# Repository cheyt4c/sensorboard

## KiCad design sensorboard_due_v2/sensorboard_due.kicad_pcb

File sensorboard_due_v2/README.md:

# Sensorboard PCB v2

## Changes from v1

 * Schematic will reflect intended PCB design, not current breadboard setup
 * More connectors need to be added on for expansion. I2C address conflict issue (for at least additional IMUs) will need to be addressed.
 * Sensor board will be generic enough to be reused multiple times if needed
 * LED panel connector fix? (missing GND wire)

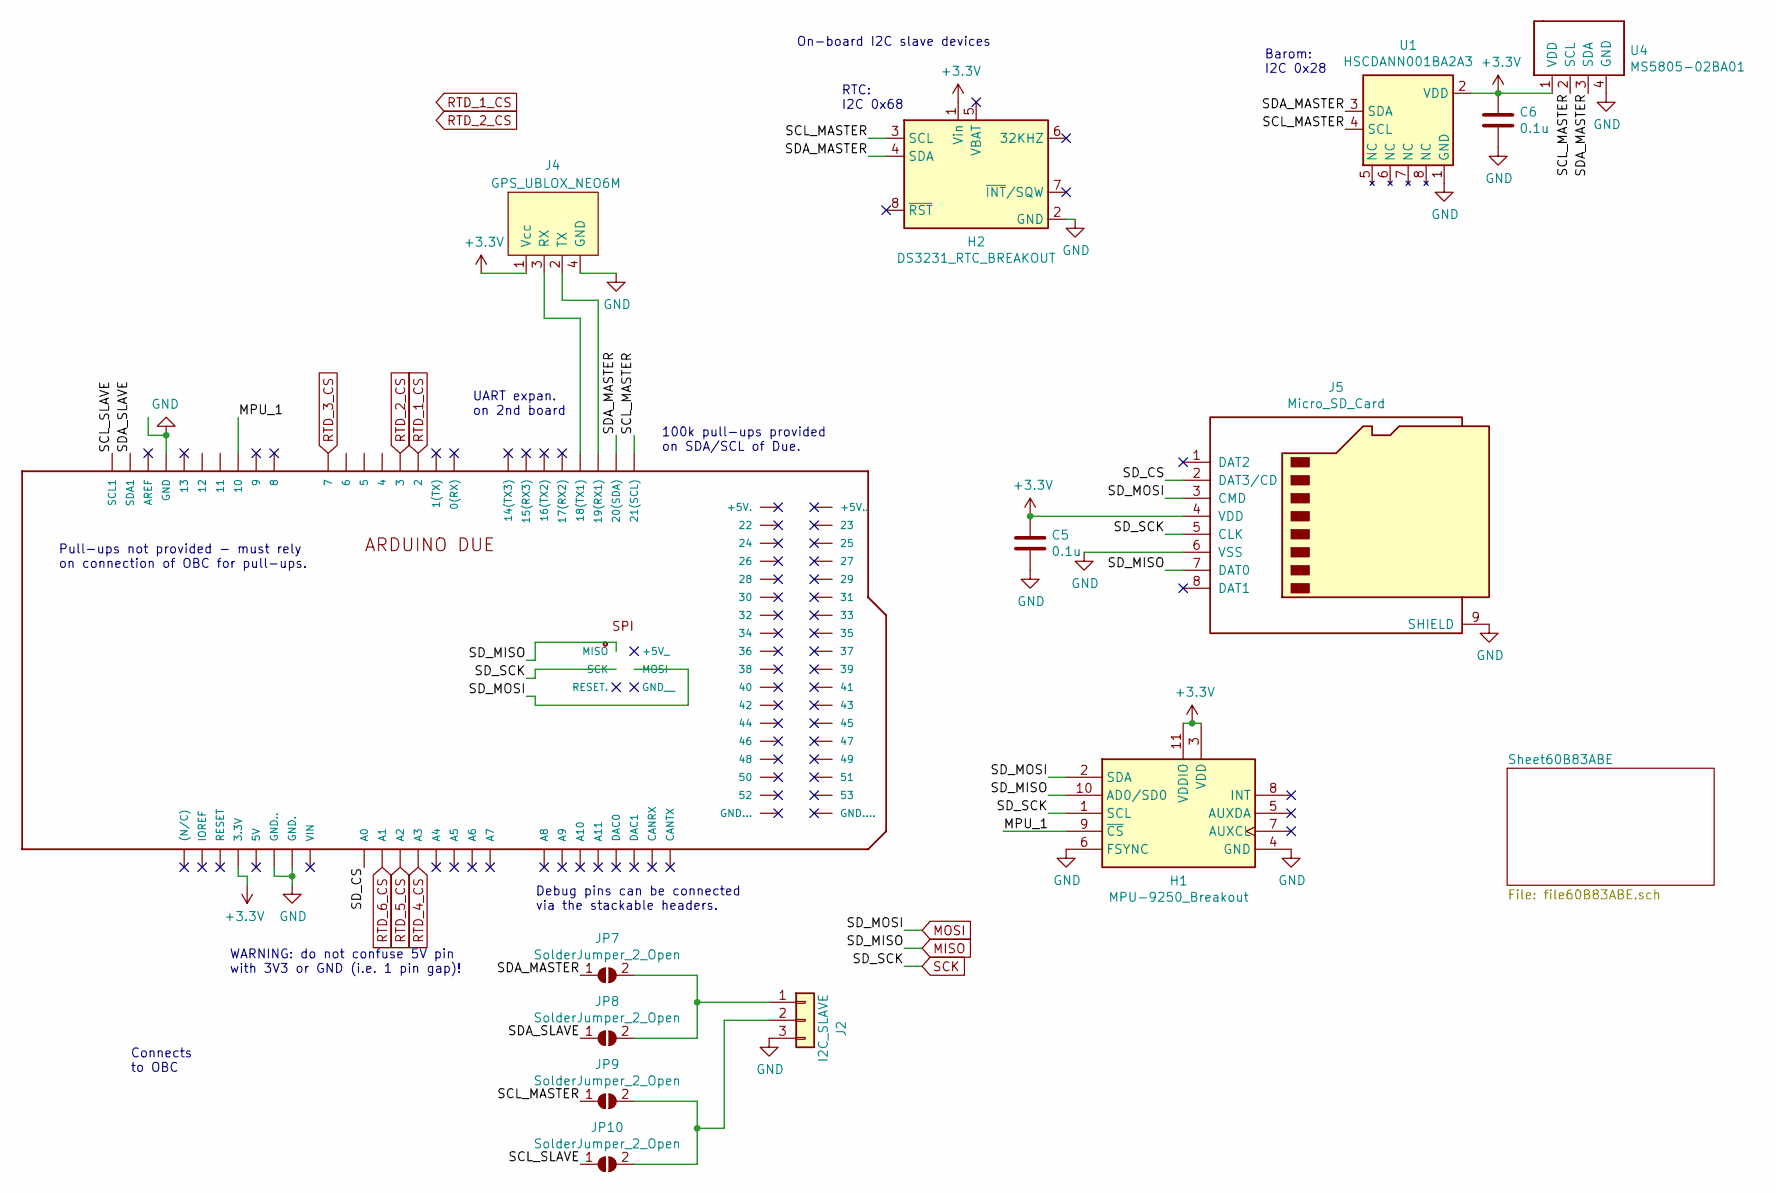
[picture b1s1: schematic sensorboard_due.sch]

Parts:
C5, C6: 0.1u; C_0805_2012Metric_Pad1.15x1.40mm_HandSolder
H1: MPU-9250_Breakout
H2: DS3231_RTC_BREAKOUT; DS3231_RTC_Breakout
J2: I2C_SLAVE; 70553-0002_3P
J4: GPS_UBLOX_NEO6M; 70553-0038_4P
J5: Micro_SD_Card; microSD_HC_Hirose_DM3BT-DSF-PEJS
JP7, JP8, JP9, JP10: SolderJumper_2_Open; SolderJumper-2_P1.3mm_Open_TrianglePad1.0x1.5mm
PCB1: ARDUINO_DUE; ARDUINO_DUE_Shield_wSPI
U1: HSCDANN001BA2A3; HSCDANN001BA2A3_DIP8
U4: MS5805-02BA01

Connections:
+3V3: C5.1, C6.1, H1.3 (VDD), H1.11 (VDDIO), H2.1 (Vin), J4.1 (Vcc), J5.4 (VDD), PCB1.3.3V, U1.2 (VDD), U4.1 (VDD); also elsewhere on the board
/MPU_1: H1.9 (~CS), PCB1.10
/SCL_MASTER: H2.3 (SCL), JP9.1 (A), PCB1.21 (21(SCL)), U1.4 (SCL), U4.2 (SCL)
/SCL_SLAVE: JP10.1 (A), PCB1.SCL1
/SDA_MASTER: H2.4 (SDA), JP7.1 (A), PCB1.20 (20(SDA)), U1.3 (SDA), U4.3 (SDA)
/SDA_SLAVE: JP8.1 (A), PCB1.SDA1
/SD_CS: J5.2 (DAT3/CD), PCB1.A0
GND: C5.2, C6.2, H1.4 (GND), H1.6 (FSYNC), H2.2 (GND), J2.3, J4.4 (GND), J5.6 (VSS), J5.9 (SHIELD), PCB1.GND, PCB1.GND., PCB1.GND.., U1.1 (GND), U4.4 (GND); also elsewhere on the board
MISO: H1.10 (AD0/SD0), J5.7 (DAT0), PCB1.MISO; also elsewhere on the board
MOSI: H1.2 (SDA), J5.3 (CMD), PCB1.MOSI; also elsewhere on the board
unnamed: J2.1, JP7.2 (B), JP8.2 (B)
unnamed: J2.2, JP9.2 (B), JP10.2 (B)
unnamed: J4.2 (TX), PCB1.19 (19(RX1))
unnamed: J4.3 (RX), PCB1.18 (18(TX1))
RTD_1_CS: PCB1.2; also elsewhere on the board
RTD_2_CS: PCB1.3; also elsewhere on the board
RTD_3_CS: PCB1.7; also elsewhere on the board
RTD_4_CS: PCB1.A3; also elsewhere on the board
RTD_5_CS: PCB1.A2; also elsewhere on the board
RTD_6_CS: PCB1.A1; also elsewhere on the board
SCK: H1.1 (SCL), J5.5 (CLK), PCB1.SCK; also elsewhere on the board

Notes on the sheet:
Connects to OBC
WARNING: do not confuse 5V pin with 3V3 or GND (i.e. 1 pin gap)!
Pull-ups not provided - must rely on connection of OBC for pull-ups.
Debug pins can be connected via the stackable headers.
Barom: I2C 0x28
On-board I2C slave devices
RTC: I2C 0x68
UART expan. on 2nd board
100k pull-ups provided on SDA/SCL of Due.

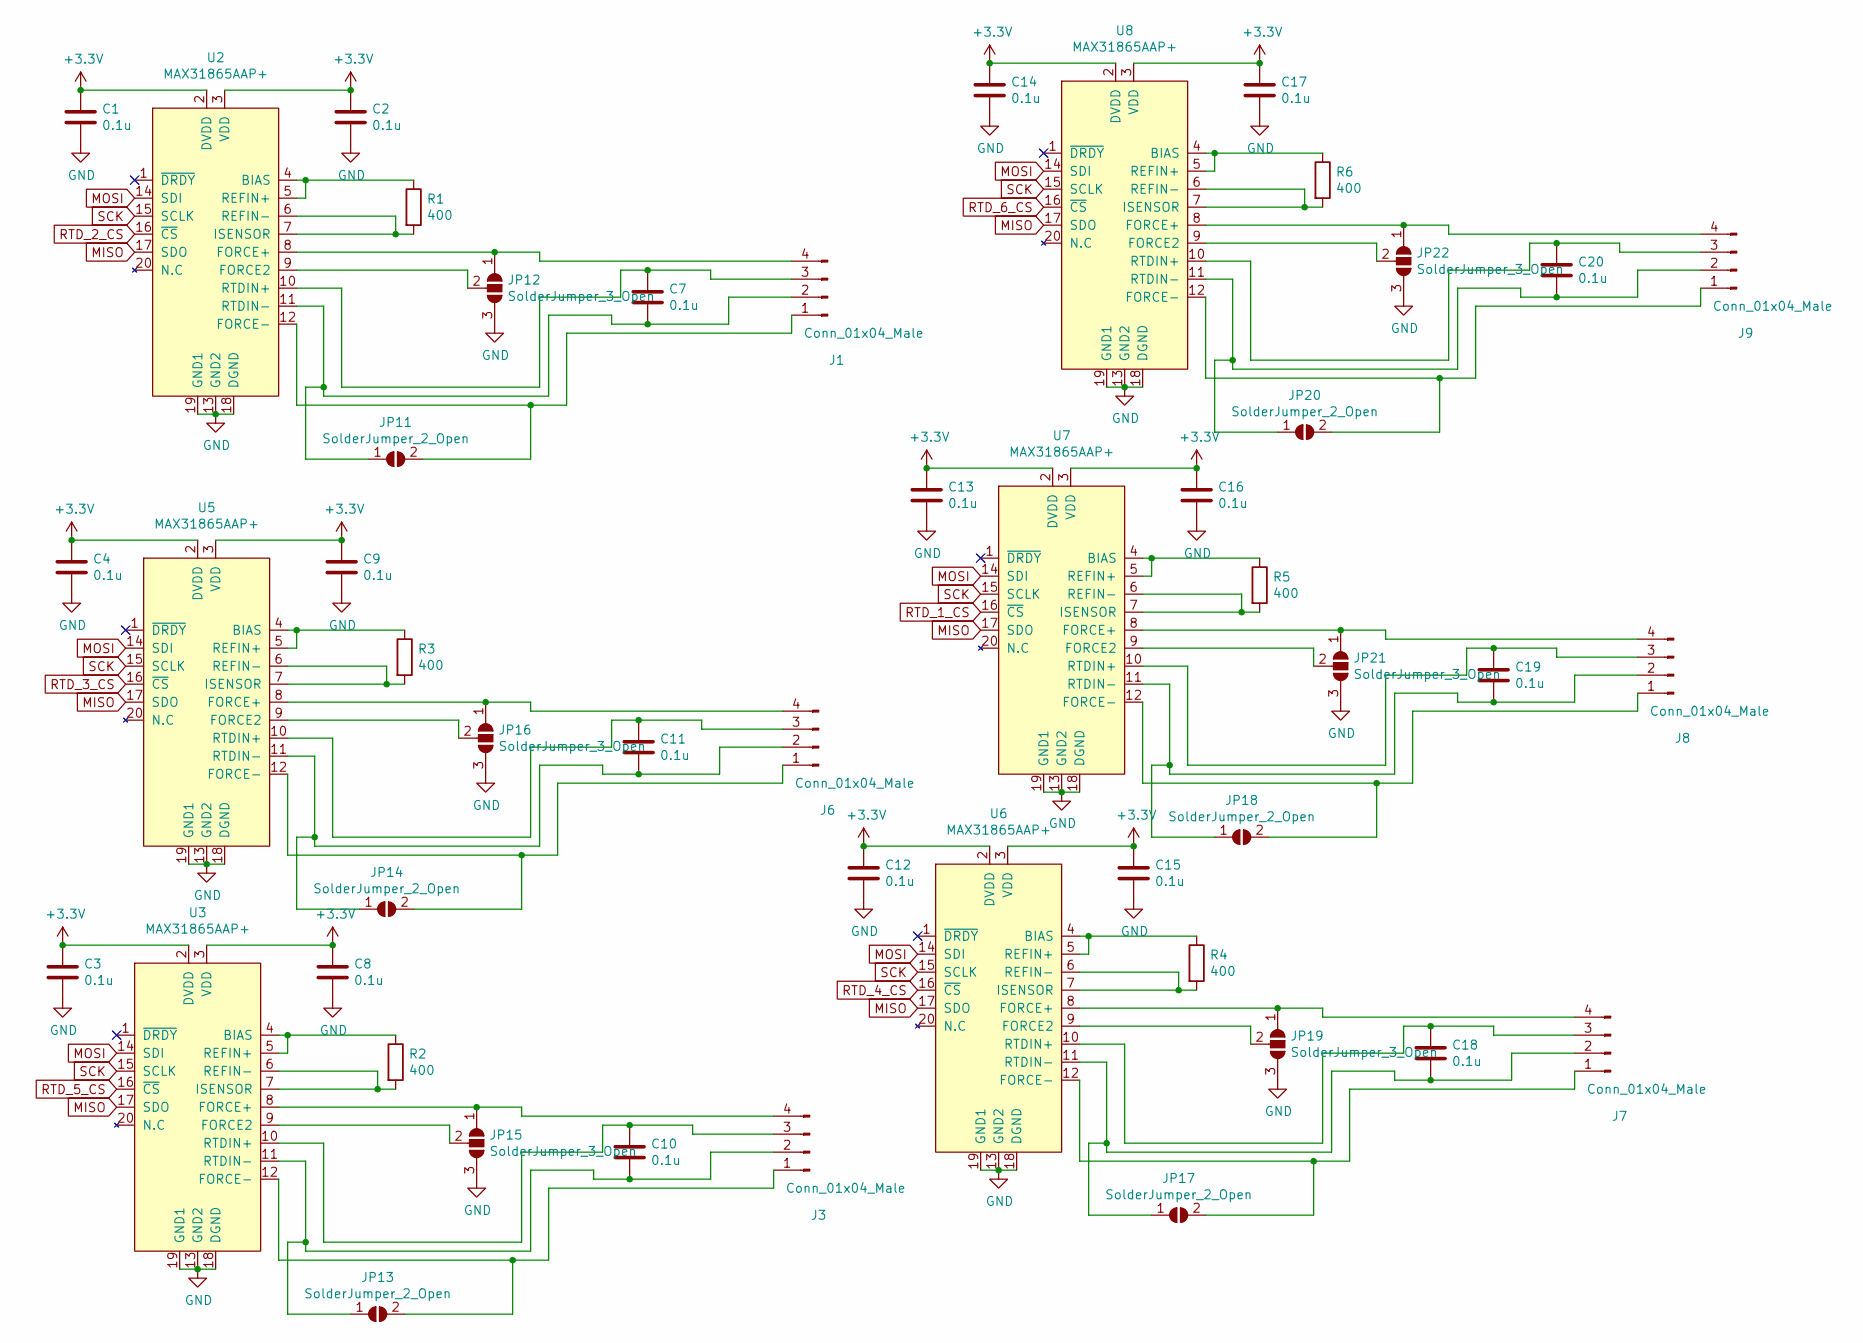
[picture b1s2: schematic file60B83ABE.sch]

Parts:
C1, C2, C3, C4, C7, C8, C9, C10, C11, C12, C13, C14, C15, C16, C17, C18, C19, C20: 0.1u; C_0805_2012Metric_Pad1.15x1.40mm_HandSolder
J1, J3, J6, J7, J8, J9: Conn_01x04_Male; JST_XH_B4B-XH-A_1x04_P2.50mm_Vertical
JP11, JP13, JP14, JP17, JP18, JP20: SolderJumper_2_Open; SolderJumper-2_P1.3mm_Open_Pad1.0x1.5mm
JP12, JP15, JP16, JP19, JP21, JP22: SolderJumper_3_Open; SolderJumper-3_P1.3mm_Open_Pad1.0x1.5mm
R1, R2, R3, R4, R5, R6: 400; R_0603_1608Metric_Pad1.05x0.95mm_HandSolder
U2, U3, U5, U6, U7, U8: MAX31865AAP+; SSOP-20_5.3x7.2mm_P0.65mm

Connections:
+3V3: C1.1, C2.1, C3.1, C4.1, C8.1, C9.1, C12.1, C13.1, C14.1, C15.1, C16.1, C17.1, U2.2 (DVDD), U2.3 (VDD), U3.2 (DVDD), U3.3 (VDD), U5.2 (DVDD), U5.3 (VDD), U6.2 (DVDD), U6.3 (VDD), U7.2 (DVDD), U7.3 (VDD), U8.2 (DVDD), U8.3 (VDD); also elsewhere on the board
GND: C1.2, C2.2, C3.2, C4.2, C8.2, C9.2, C12.2, C13.2, C14.2, C15.2, C16.2, C17.2, JP12.3 (B), JP15.3 (B), JP16.3 (B), JP19.3 (B), JP21.3 (B), JP22.3 (B), U2.13 (GND2), U2.18 (DGND), U2.19 (GND1), U3.13 (GND2), U3.18 (DGND), U3.19 (GND1), U5.13 (GND2), U5.18 (DGND), U5.19 (GND1), U6.13 (GND2), U6.18 (DGND), U6.19 (GND1), U7.13 (GND2), U7.18 (DGND), U7.19 (GND1), U8.13 (GND2), U8.18 (DGND), U8.19 (GND1); also elsewhere on the board
MISO: U2.17 (SDO), U3.17 (SDO), U5.17 (SDO), U6.17 (SDO), U7.17 (SDO), U8.17 (SDO); also elsewhere on the board
MOSI: U2.14 (SDI), U3.14 (SDI), U5.14 (SDI), U6.14 (SDI), U7.14 (SDI), U8.14 (SDI); also elsewhere on the board
unnamed: C7.1, J1.3, U2.10 (RTDIN+)
unnamed: C7.2, J1.2, JP11.1 (A), U2.11 (RTDIN-)
unnamed: C10.1, J3.3, U3.10 (RTDIN+)
unnamed: C10.2, J3.2, JP13.1 (A), U3.11 (RTDIN-)
unnamed: C11.1, J6.3, U5.10 (RTDIN+)
unnamed: C11.2, J6.2, JP14.1 (A), U5.11 (RTDIN-)
unnamed: C18.1, J7.3, U6.10 (RTDIN+)
unnamed: C18.2, J7.2, JP17.1 (A), U6.11 (RTDIN-)
unnamed: C19.1, J8.3, U7.10 (RTDIN+)
unnamed: C19.2, J8.2, JP18.1 (A), U7.11 (RTDIN-)
unnamed: C20.1, J9.3, U8.10 (RTDIN+)
unnamed: C20.2, J9.2, JP20.1 (A), U8.11 (RTDIN-)
unnamed: J1.1, JP11.2 (B), U2.12 (FORCE-)
unnamed: J1.4, JP12.1 (A), U2.8 (FORCE+)
unnamed: J3.1, JP13.2 (B), U3.12 (FORCE-)
unnamed: J3.4, JP15.1 (A), U3.8 (FORCE+)
unnamed: J6.1, JP14.2 (B), U5.12 (FORCE-)
unnamed: J6.4, JP16.1 (A), U5.8 (FORCE+)
unnamed: J7.1, JP17.2 (B), U6.12 (FORCE-)
unnamed: J7.4, JP19.1 (A), U6.8 (FORCE+)
unnamed: J8.1, JP18.2 (B), U7.12 (FORCE-)
unnamed: J8.4, JP21.1 (A), U7.8 (FORCE+)
unnamed: J9.1, JP20.2 (B), U8.12 (FORCE-)
unnamed: J9.4, JP22.1 (A), U8.8 (FORCE+)
unnamed: JP12.2 (C), U2.9 (FORCE2)
unnamed: JP15.2 (C), U3.9 (FORCE2)
unnamed: JP16.2 (C), U5.9 (FORCE2)
unnamed: JP19.2 (C), U6.9 (FORCE2)
unnamed: JP21.2 (C), U7.9 (FORCE2)
unnamed: JP22.2 (C), U8.9 (FORCE2)
unnamed: R1.1, U2.4 (BIAS), U2.5 (REFIN+)
unnamed: R1.2, U2.6 (REFIN-), U2.7 (ISENSOR)
unnamed: R2.1, U3.4 (BIAS), U3.5 (REFIN+)
unnamed: R2.2, U3.6 (REFIN-), U3.7 (ISENSOR)
unnamed: R3.1, U5.4 (BIAS), U5.5 (REFIN+)
unnamed: R3.2, U5.6 (REFIN-), U5.7 (ISENSOR)
unnamed: R4.1, U6.4 (BIAS), U6.5 (REFIN+)
unnamed: R4.2, U6.6 (REFIN-), U6.7 (ISENSOR)
unnamed: R5.1, U7.4 (BIAS), U7.5 (REFIN+)
unnamed: R5.2, U7.6 (REFIN-), U7.7 (ISENSOR)
unnamed: R6.1, U8.4 (BIAS), U8.5 (REFIN+)
unnamed: R6.2, U8.6 (REFIN-), U8.7 (ISENSOR)
RTD_1_CS: U7.16 (~CS); also elsewhere on the board
RTD_2_CS: U2.16 (~CS); also elsewhere on the board
RTD_3_CS: U5.16 (~CS); also elsewhere on the board
RTD_4_CS: U6.16 (~CS); also elsewhere on the board
RTD_5_CS: U3.16 (~CS); also elsewhere on the board
RTD_6_CS: U8.16 (~CS); also elsewhere on the board
SCK: U2.15 (SCLK), U3.15 (SCLK), U5.15 (SCLK), U6.15 (SCLK), U7.15 (SCLK), U8.15 (SCLK); also elsewhere on the board

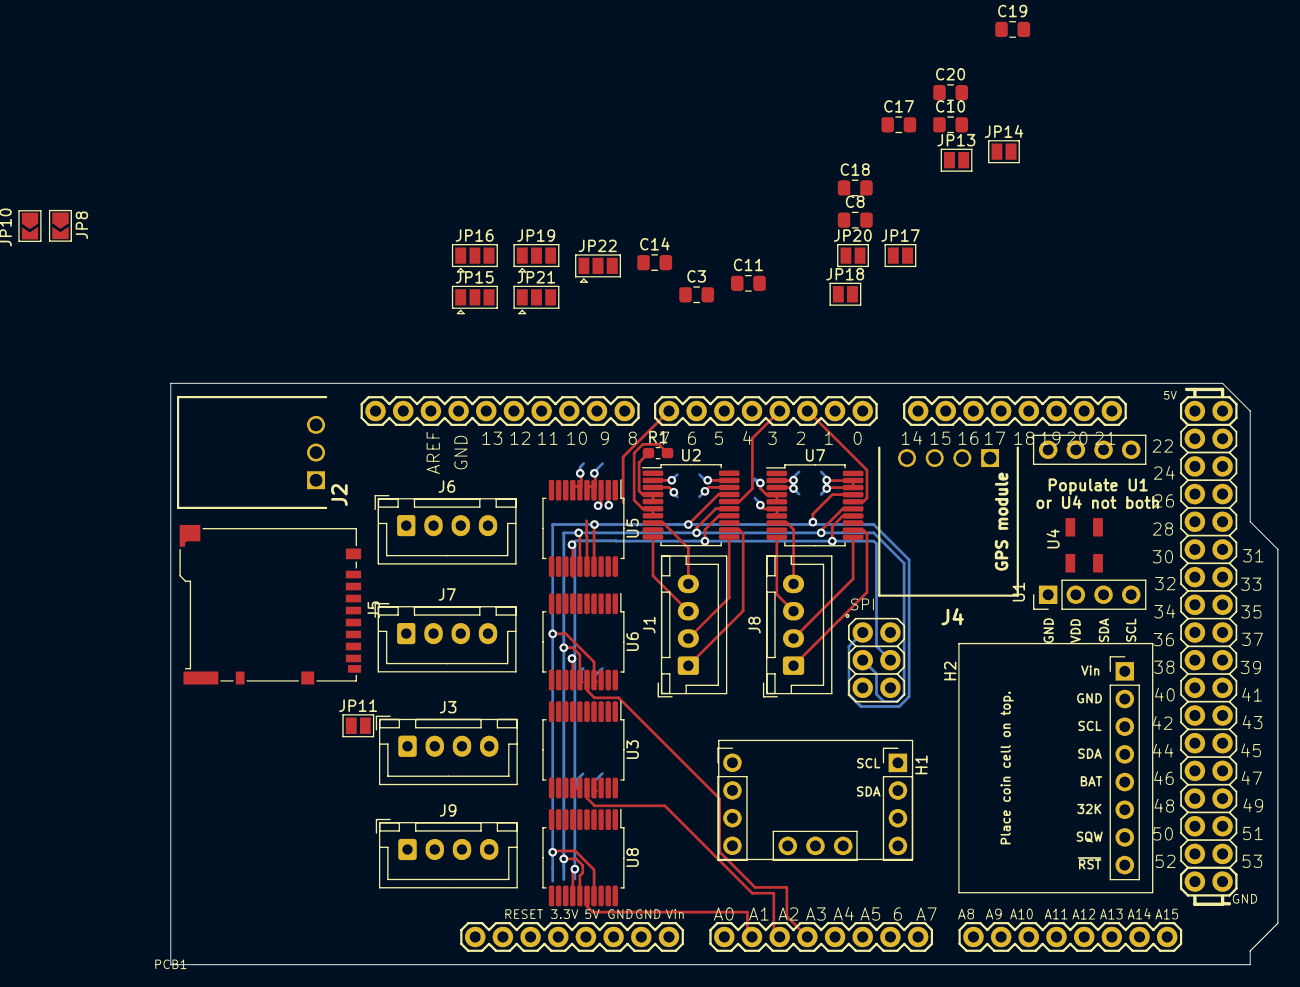
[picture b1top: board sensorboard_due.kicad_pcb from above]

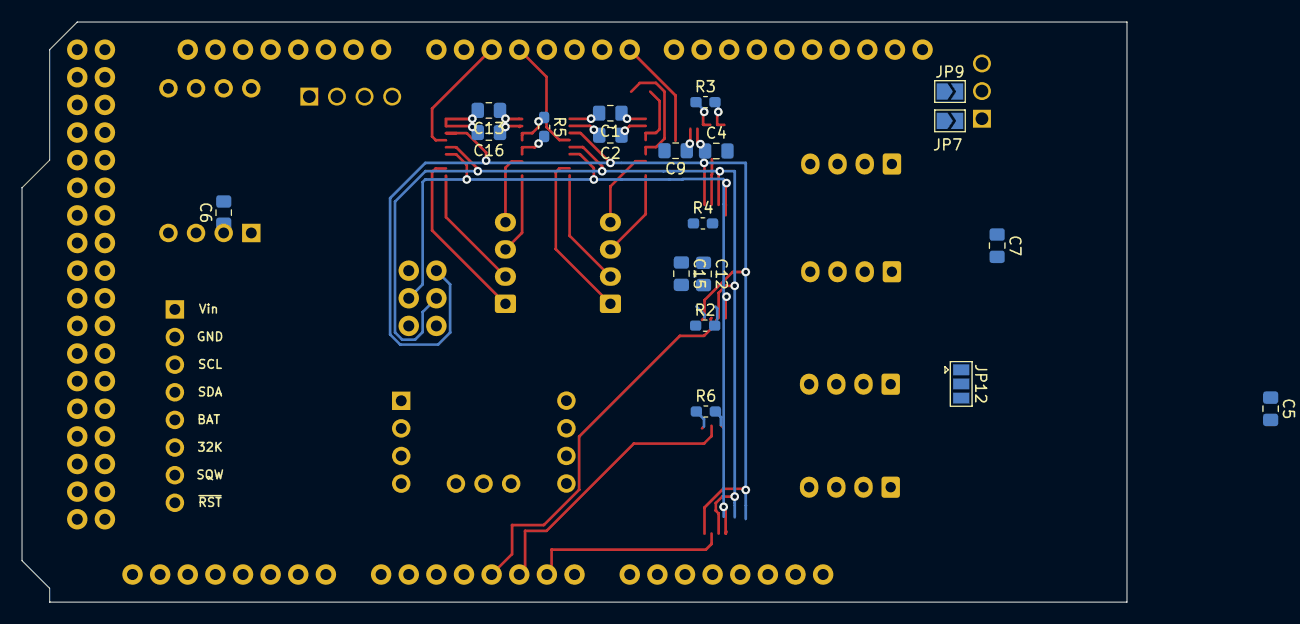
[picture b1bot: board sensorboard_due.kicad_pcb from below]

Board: 4 copper layers, 101.6 x 53.3 mm, 62 parts (19 on the bottom side), 63 nets.

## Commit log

2019-12-05 Add ICSP header and level converter library
2019-12-05 Add level converters for SPI and I2C busses
2019-12-05 Add internal DHT22 sensor
2019-12-05 Add SD card breakout board
2019-12-05 Add MPU-9250 breakout board footprint
2019-12-05 Change description
2019-12-05 Rename 3v3 nets to 3V3
2019-12-05 Add HSCDANN001BA2A3 sensor footprint
2019-12-05 Change datasheet for barometer sensor
2019-12-05 Add all onboard sensors
    The sensors are:
    Barometer sensor
    DHT22 sensor
    DS3231 RTC
2019-12-05 Add indicator LED array and external sensor connector
2019-12-14 Add more sensors
2020-01-24 due schematic
2020-01-24 working electrical rules - but a bit hacky
2020-01-31 strongly regret not doing it in kicad
2020-02-03 need way more stuff on pcb?
2020-02-05 pcb footprints for breadboard components should be accurate to datasheet (callipers if no ds) now
2020-02-07 downloaded molex conns online and added; changes made for pin labelling consistency
2020-02-07 slight molex conn footprint changes for manuf consistency
2020-02-08 modified molex connectors to be datasheet compliant
2020-02-14 quick sketch of perf board v2
2020-02-20 halfway through ... need to route pcb
2021-02-03 Sync
2021-05-20 asdasd
2021-06-03 PCB layout
2021-06-25 stuff
2021-06-25 incomplete pcb layout
